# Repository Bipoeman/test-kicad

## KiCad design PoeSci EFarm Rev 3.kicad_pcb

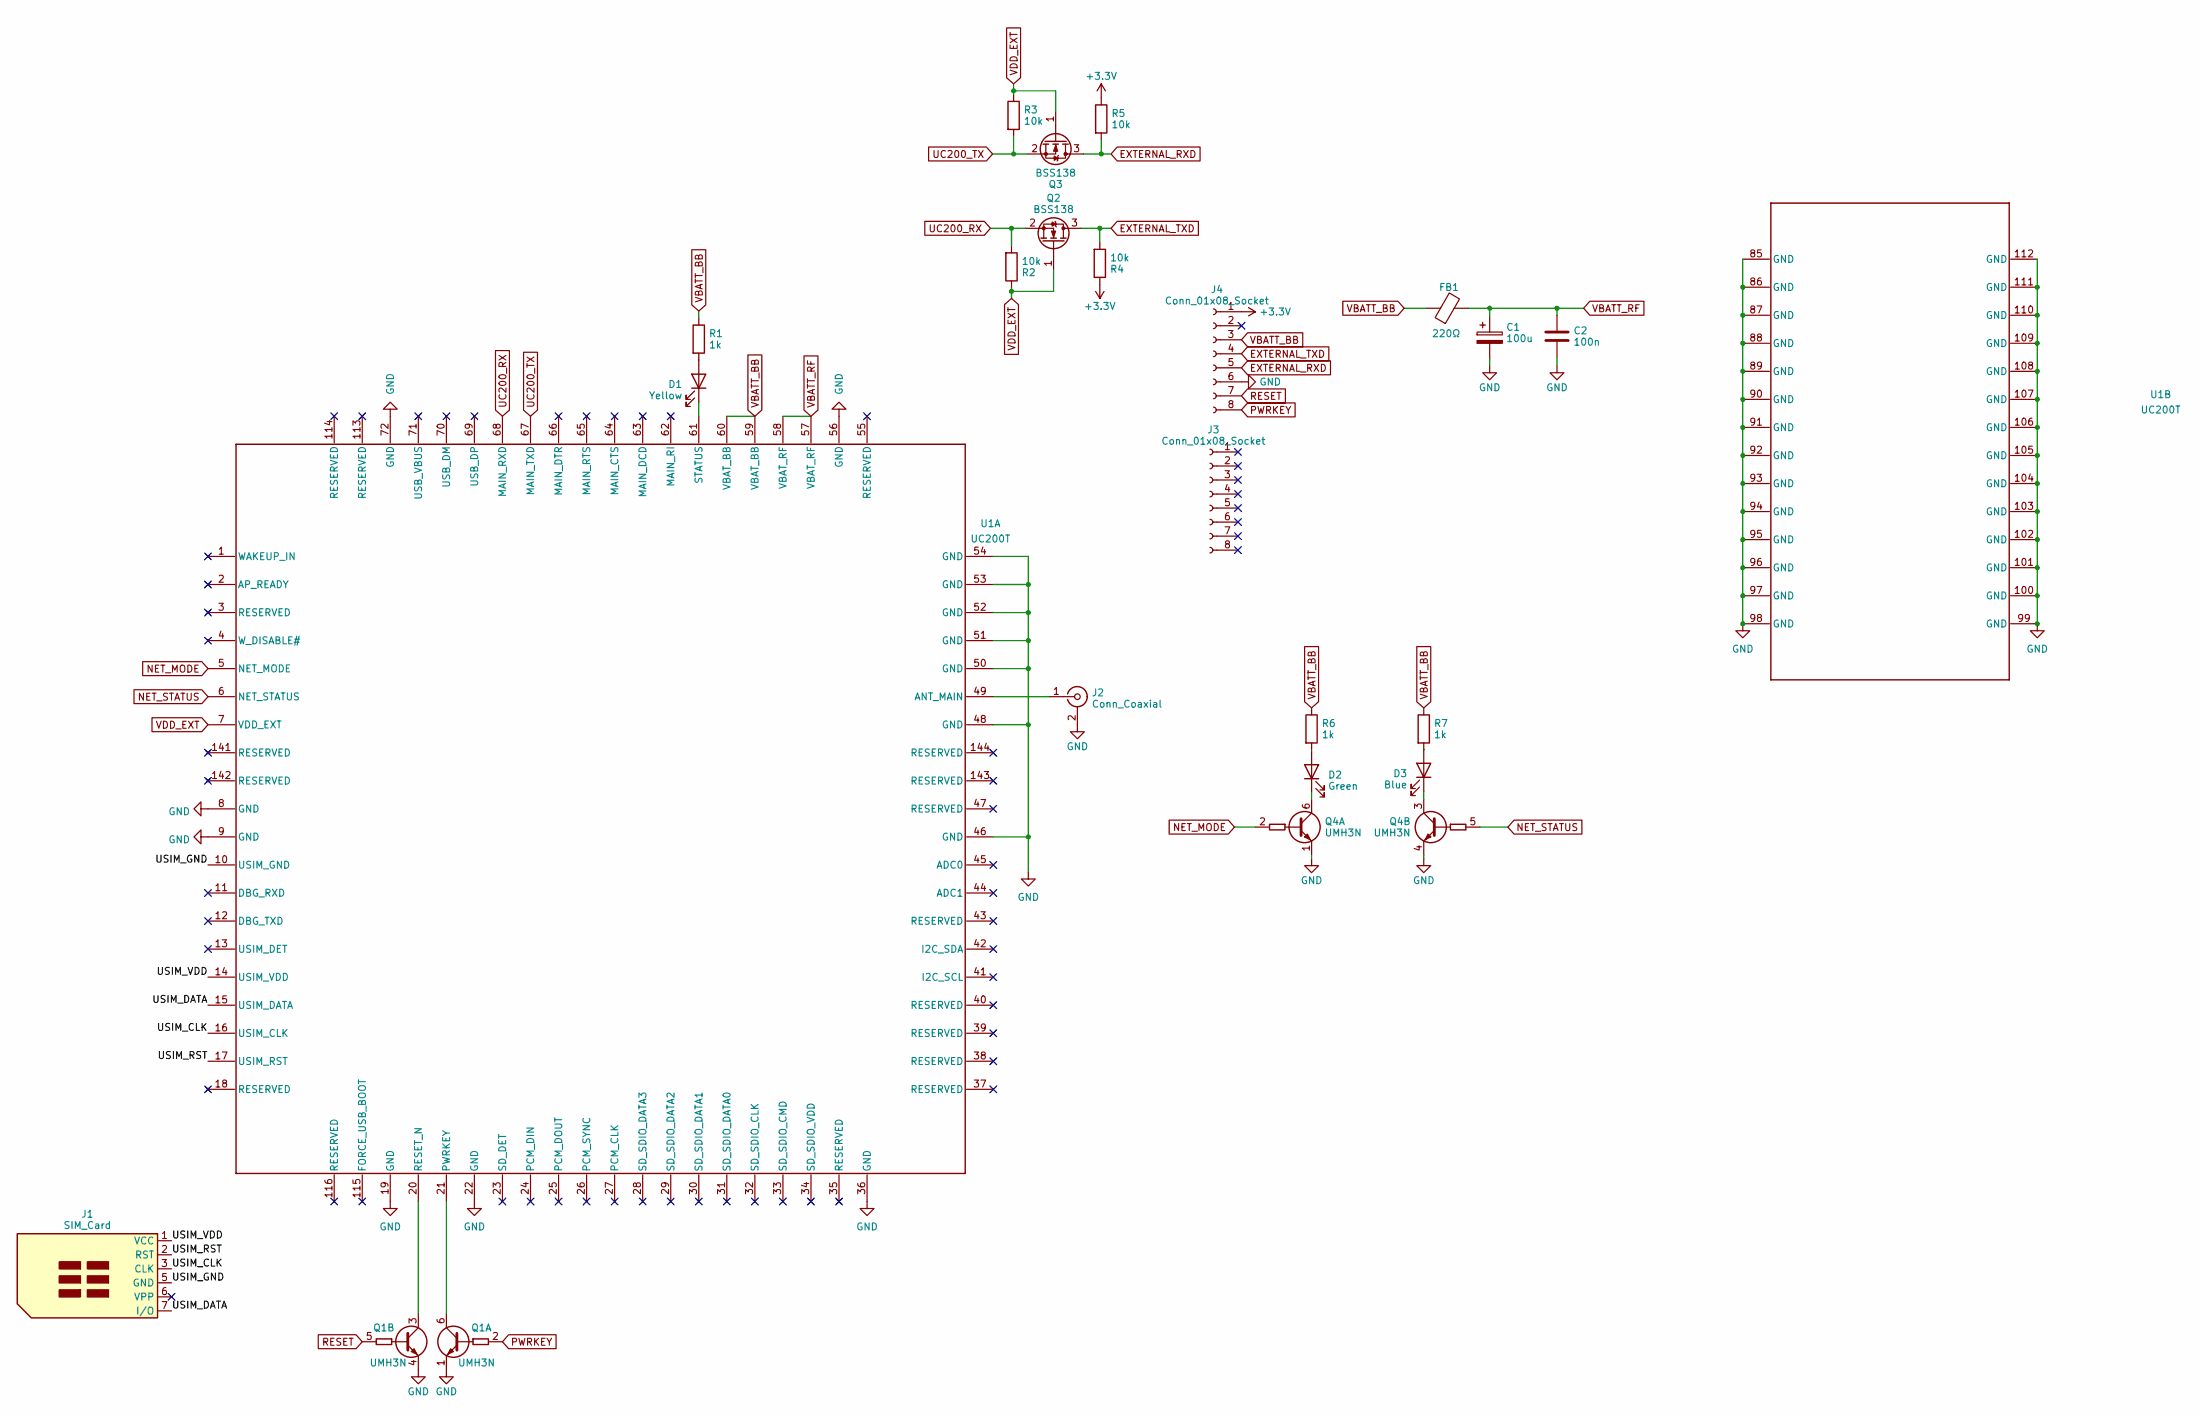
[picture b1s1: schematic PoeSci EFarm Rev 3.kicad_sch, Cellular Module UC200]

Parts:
C1: 100u; CP_Elec_6.3x5.4
C2: 100n; C_0603_1608Metric_Pad1.08x0.95mm_HandSolder
D1: Yellow; LED_0603_1608Metric_Pad1.05x0.95mm_HandSolder
D2: Green; LED_0603_1608Metric_Pad1.05x0.95mm_HandSolder
D3: Blue; LED_0603_1608Metric_Pad1.05x0.95mm_HandSolder
FB1: 220Ω; L_0805_2012Metric_Pad1.15x1.40mm_HandSolder
J1: SIM_Card; HOAUC HYC14-SIM07-135B
J2: Conn_Coaxial; SMA_Amphenol_901-143_Horizontal
J3, J4: Conn_01x08_Socket; PinSocket_1x08_P2.54mm_Vertical
Q1, Q4: UMH3N; SOT-363_SC-70-6
Q2, Q3: BSS138; SOT-23
R1, R6, R7: 1k; R_0603_1608Metric_Pad0.98x0.95mm_HandSolder
R2, R3, R4, R5: 10k; R_0603_1608Metric_Pad0.98x0.95mm_HandSolder
U1: UC200T

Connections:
+3.3V: J4.1, R4.1, R5.1
/USIM_CLK: J1.3 (CLK), U1.16 (USIM_CLK)
/USIM_DATA: J1.7 (I/O), U1.15 (USIM_DATA)
/USIM_GND: J1.5 (GND), U1.10 (USIM_GND)
/USIM_RST: J1.2 (RST), U1.17 (USIM_RST)
/USIM_VDD: J1.1 (VCC), U1.14 (USIM_VDD)
EXTERNAL_RXD: J4.5, Q3.3 (D), R5.2
EXTERNAL_TXD: J4.4, Q2.3 (D), R4.2
GND: C1.2, C2.2, J2.2 (Ext), J4.6, Q1.1 (E1), Q1.4 (E2), Q4.1 (E1), Q4.4 (E2), U1.8 (GND), U1.9 (GND), U1.19 (GND), U1.22 (GND), U1.36 (GND), U1.46 (GND), U1.48 (GND), U1.50 (GND), U1.51 (GND), U1.52 (GND), U1.53 (GND), U1.54 (GND), U1.56 (GND), U1.72 (GND), U1.85 (GND), U1.86 (GND), U1.87 (GND), U1.88 (GND), U1.89 (GND), U1.90 (GND), U1.91 (GND), U1.92 (GND), U1.93 (GND), U1.94 (GND), U1.95 (GND), U1.96 (GND), U1.97 (GND), U1.98 (GND), U1.99 (GND), U1.100 (GND), U1.101 (GND), U1.102 (GND), U1.103 (GND), U1.104 (GND), U1.105 (GND), U1.106 (GND), U1.107 (GND), U1.108 (GND), U1.109 (GND), U1.110 (GND), U1.111 (GND), U1.112 (GND)
NET_MODE: Q4.2 (B1), U1.5 (NET_MODE)
NET_STATUS: Q4.5 (B2), U1.6 (NET_STATUS)
unnamed: D1.2 (A), R1.2
unnamed: D1.1 (K), U1.61 (STATUS)
unnamed: D2.2 (A), R6.2
unnamed: D2.1 (K), Q4.6 (C1)
unnamed: D3.2 (A), R7.2
unnamed: D3.1 (K), Q4.3 (C2)
unnamed: J2.1 (In), U1.49 (ANT_MAIN)
unnamed: Q1.6 (C1), U1.21 (PWRKEY)
unnamed: Q1.3 (C2), U1.20 (RESET_N)
PWRKEY: J4.8, Q1.2 (B1)
RESET: J4.7, Q1.5 (B2)
UC200_RX: Q2.2 (S), R2.2, U1.68 (MAIN_RXD)
UC200_TX: Q3.2 (S), R3.2, U1.67 (MAIN_TXD)
VBATT_BB: FB1.1, J4.3, R1.1, R6.1, R7.1, U1.59 (VBAT_BB), U1.60 (VBAT_BB)
VBATT_RF: C1.1, C2.1, FB1.2, U1.57 (VBAT_RF), U1.58 (VBAT_RF)
VDD_EXT: Q2.1 (G), Q3.1 (G), R2.1, R3.1, U1.7 (VDD_EXT)

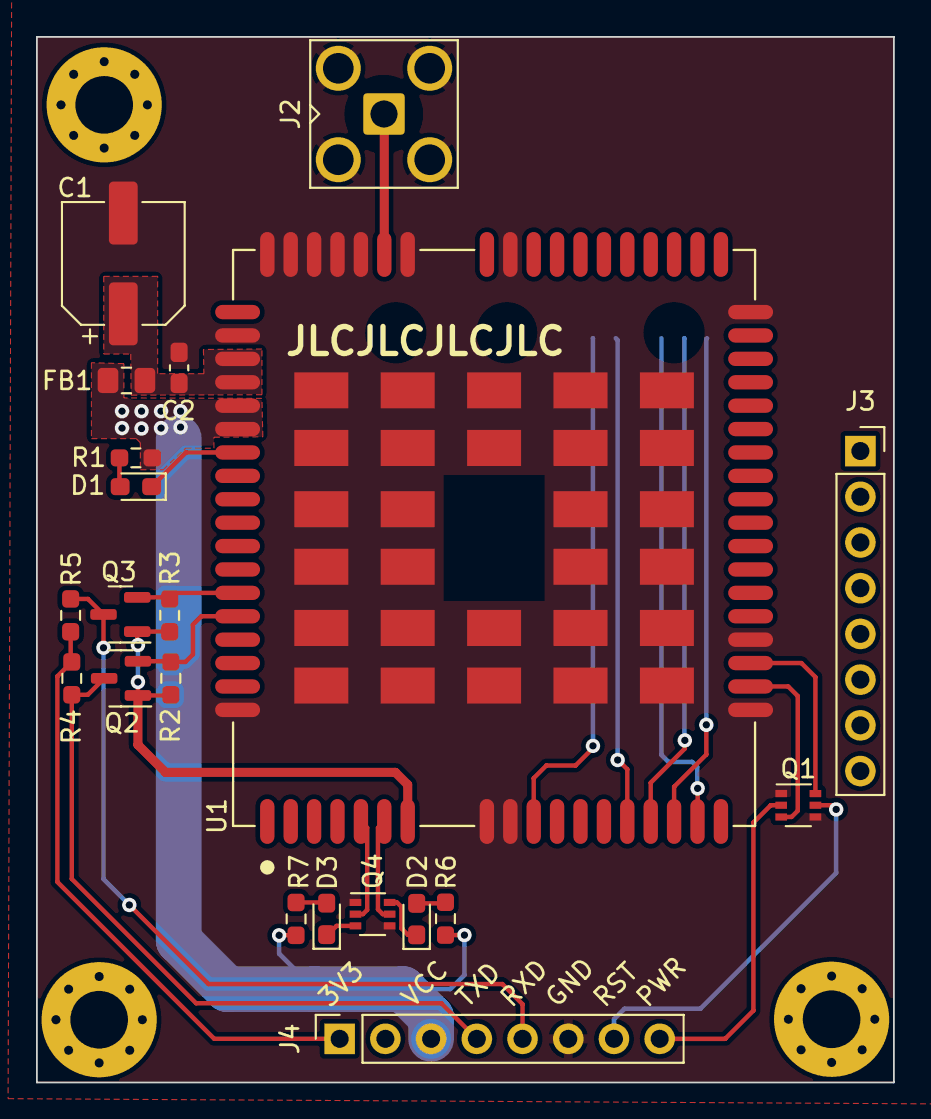
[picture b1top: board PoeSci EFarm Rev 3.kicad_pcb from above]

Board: 2 copper layers, 47.6 x 58.1 mm, 22 parts (1 on the bottom side), 27 nets.

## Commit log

2025-03-09 Initial Commit (First rev)
2025-03-09 Change position a bit
2025-03-09 add gitignore
2025-03-10 import and update 3d model
